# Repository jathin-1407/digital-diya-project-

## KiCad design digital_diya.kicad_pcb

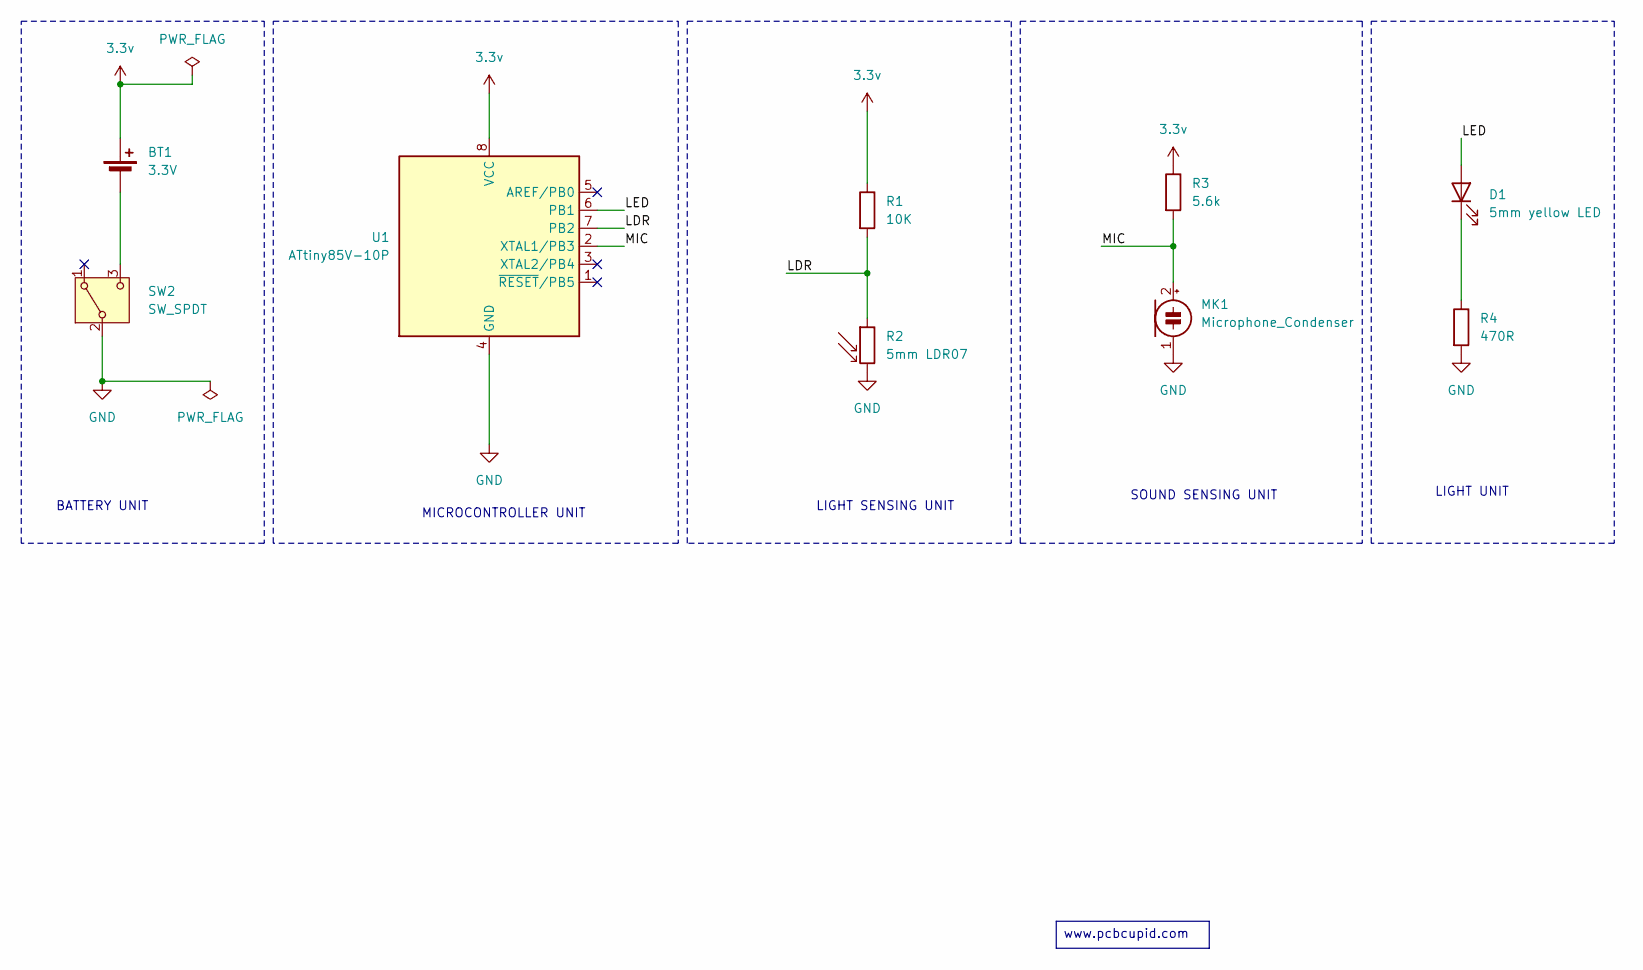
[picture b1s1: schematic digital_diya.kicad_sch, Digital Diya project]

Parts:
BT1: 3.3V; BatteryHolder_ComfortableElectronic_CH273-2450_1x2450
D1: 5mm yellow LED; LED_D5.0mm
MK1: Microphone_Condenser; PinHeader_1x02_P2.54mm_Vertical
R1: 10K; R_Axial_DIN0207_L6.3mm_D2.5mm_P15.24mm_Horizontal
R2: 5mm LDR07; R_LDR_5.1x4.3mm_P3.4mm_Vertical
R3: 5.6k; R_Axial_DIN0207_L6.3mm_D2.5mm_P15.24mm_Horizontal
R4: 470R; R_Axial_DIN0207_L6.3mm_D2.5mm_P15.24mm_Horizontal
SW2: SW_SPDT; SW_Slide_SPDT_Straight_CK_OS102011MS2Q
U1: ATtiny85V-10P; DIP-8_W7.62mm

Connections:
3.3v: BT1.1 (+), R1.1, R3.1, U1.8 (VCC)
/LDR: R1.2, R2.1, U1.7 (PB2)
/LED: D1.2 (A), U1.6 (PB1)
/MIC: MK1.2 (+), R3.2, U1.2 (XTAL1/PB3)
GND: MK1.1 (-), R2.2, R4.2, SW2.2 (B), U1.4 (GND)
unnamed: BT1.2 (-), SW2.3 (C)
unnamed: D1.1 (K), R4.1

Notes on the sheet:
LIGHT SENSING UNIT
MICROCONTROLLER UNIT
LIGHT UNIT
SOUND SENSING UNIT
BATTERY UNIT
www.pcbcupid.com

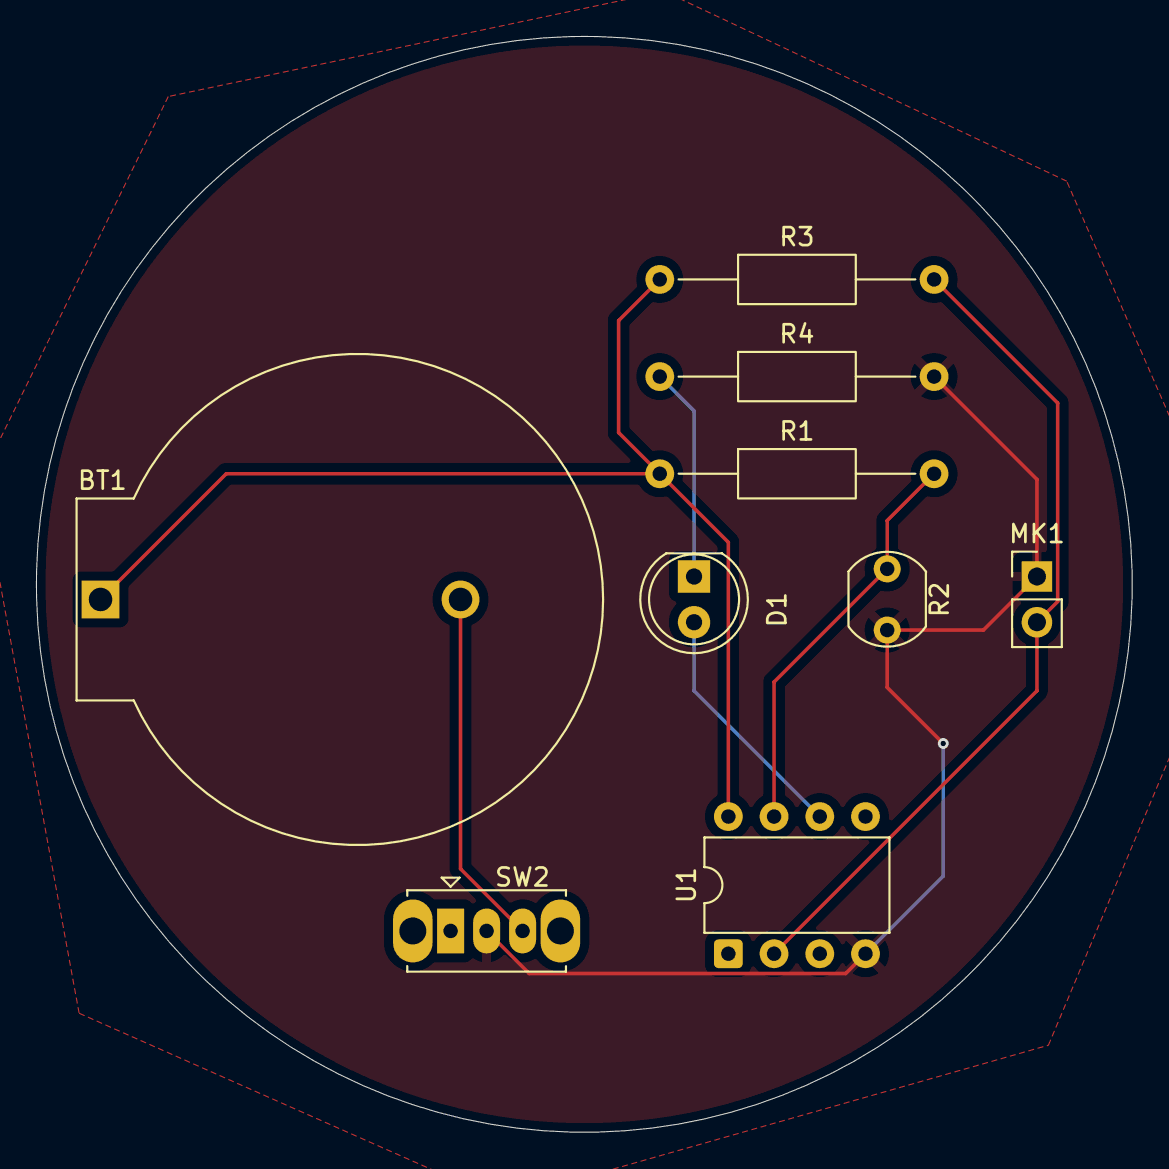
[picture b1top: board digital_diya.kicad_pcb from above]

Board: 2 copper layers, 60.9 x 60.9 mm, 9 parts (0 on the bottom side), 7 nets.

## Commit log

2025-11-17 Jathin First File
2025-11-17 Digital Divya
2025-11-17 Jathin Git
2025-11-17 pcb order
